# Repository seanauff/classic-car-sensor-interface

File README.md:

classic-car-sensor-interface
============================
Software to collect and display automotive sensor data on 16x2 LCD.
Written for use on Arduino MEGA2560, requires additional hardware to run.

Imgur album with pictures: https://imgur.com/gallery/zIYda

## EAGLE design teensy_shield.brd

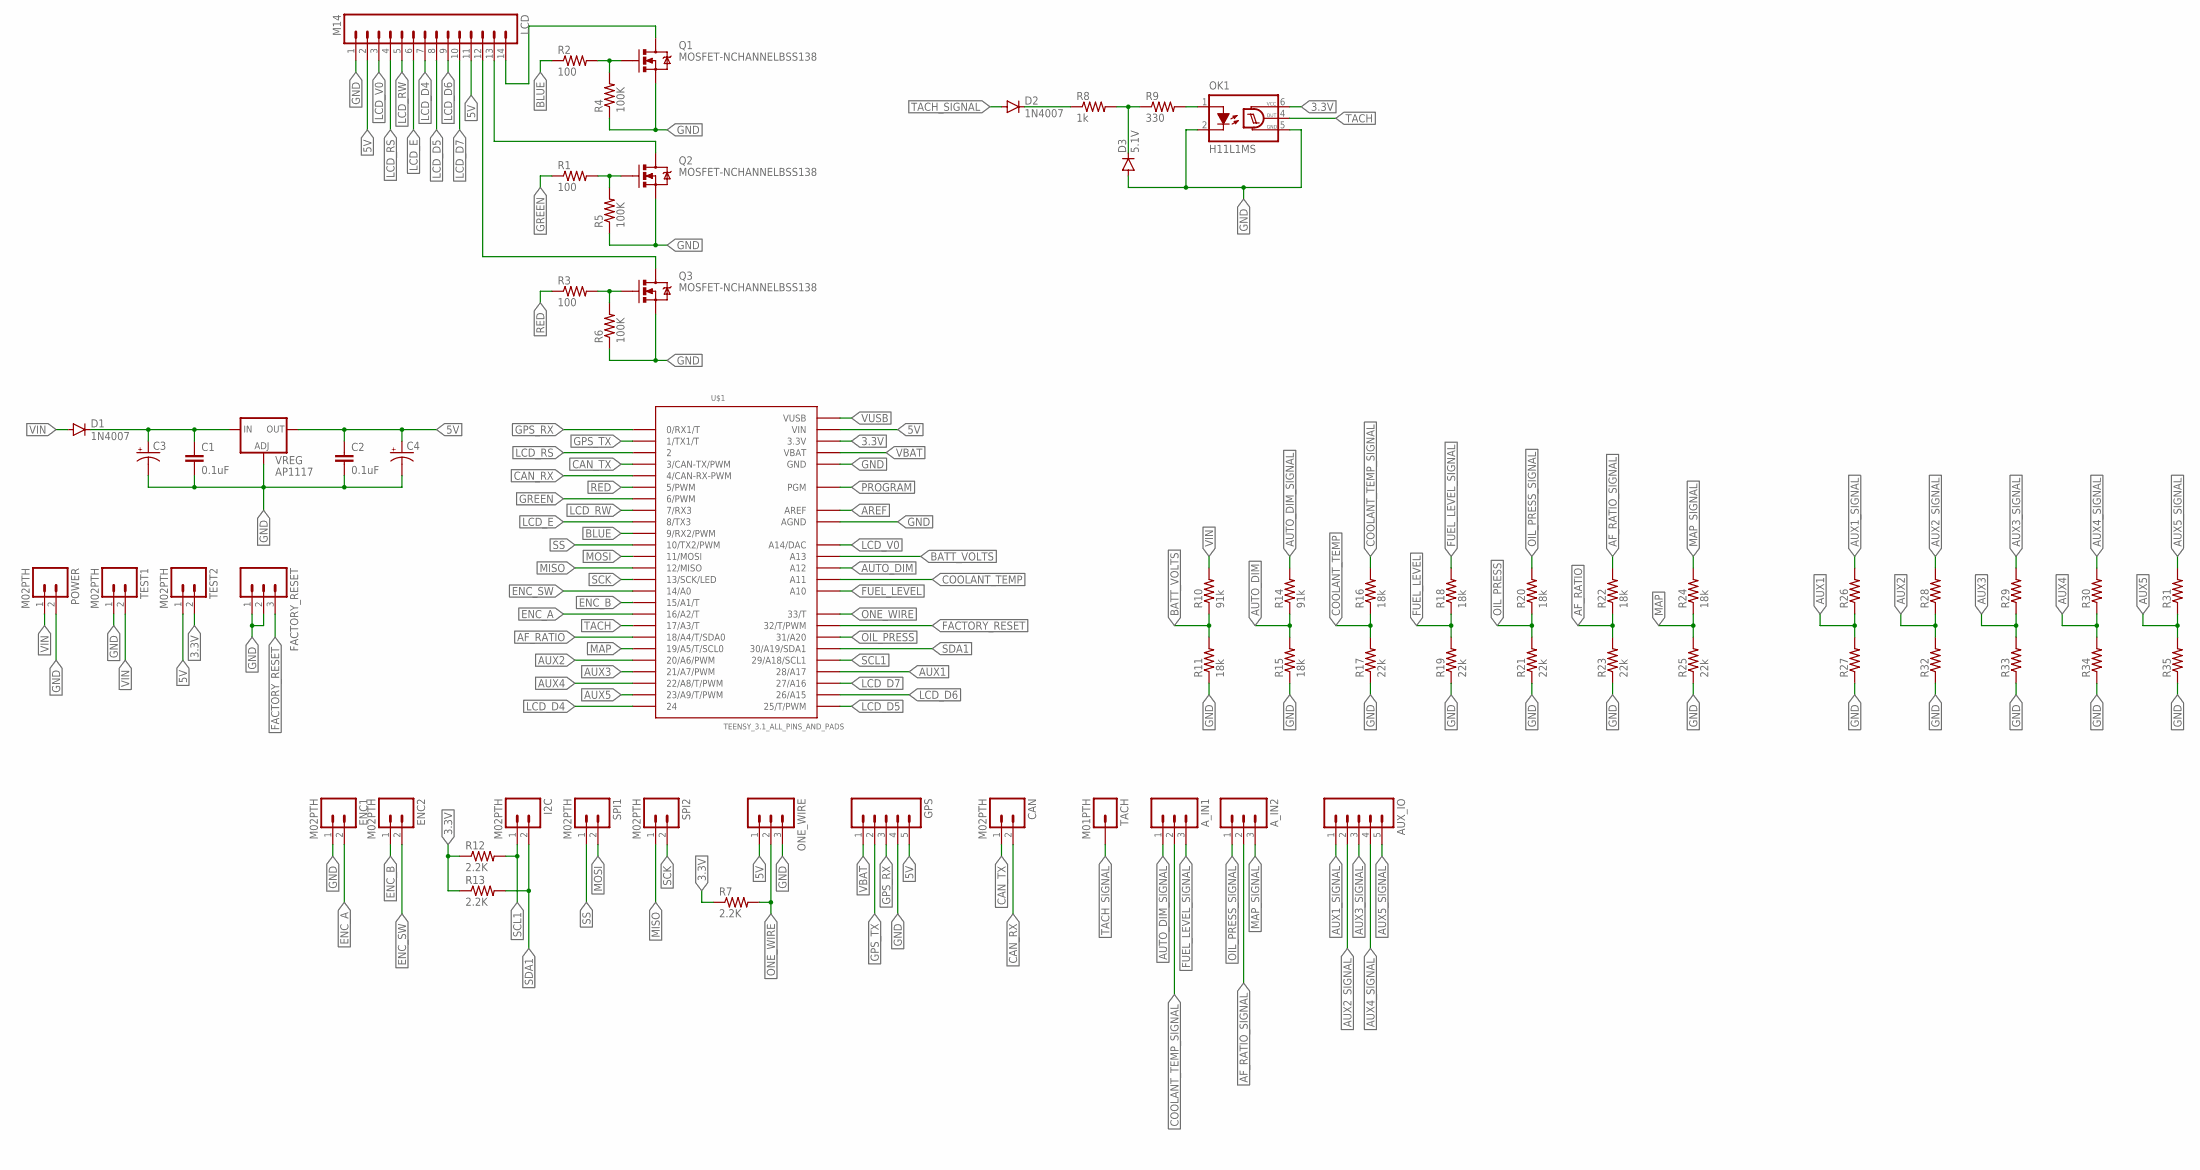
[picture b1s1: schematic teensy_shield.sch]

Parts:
AUX_IO: M05PTH; 1X05
A_IN1, A_IN2: M03PTH; 1X03
C1, C2: 0.1uF; 1206
C3, C4: CAP_POL6032; EIA6032
CAN: M02PTH; 1X02
D1, D2: 1N4007; SMA-DIODE_ALT
D3: 5.1V; SMA-DIODE_ALT
ENC1, ENC2: M02PTH; 1X02
FACTORY_RESET: M03PTH; 1X03
GPS: M05PTH; 1X05
I2C: M02PTH; 1X02
LCD: M14; 1X14
OK1: H11L1MS; DIL6-SMD
ONE_WIRE: M03PTH; 1X03
POWER: M02PTH; 1X02
Q1, Q2, Q3: MOSFET-NCHANNELBSS138; SOT23
R1, R2, R3: 100; 1206
R4, R5, R6: 100K; 1206
R7, R12, R13: 2.2K; 1206
R8: 1k; 1206
R9: 330; 1206
R10, R14: 91k; 1206
R11, R15, R16, R18, R20, R22, R24: 18k; 1206
R17, R19, R21, R23, R25: 22k; 1206
R26, R27, R28, R29, R30, R31, R32, R33, R34, R35: RESISTOR1206; 1206
SPI1, SPI2: M02PTH; 1X02
TACH: M01PTH; 1X01
TEST1, TEST2: M02PTH; 1X02
U$1: TEENSY_3.1_ALL_PINS_AND_PADS; TEENSY_3.1_ALLPINS
VREG: AP1117; SOT223

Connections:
3.3V: OK1.6 (VCC), R7.1, R12.1, R13.1, TEST2.2, U$1.3.3V, U$1.3.3V1 (3.3V), U$1.3.3V2 (3.3V)
5V: C2.1, C4.P$1 (+), GPS.5, LCD.2, LCD.11, ONE_WIRE.1, TEST2.1, U$1.VIN, VREG.2 (OUT)
AF_RATIO: R22.1, R23.2, U$1.18/A4 (18/A4/T/SDA0)
AF_RATIO_SIGNAL: A_IN2.2, R22.2
AREF: U$1.AREF
AUTO_DIM: R14.1, R15.2, U$1.A12
AUTO_DIM_SIGNAL: A_IN1.1, R14.2
AUX1: R26.1, R27.2, U$1.28 (28/A17)
AUX1_SIGNAL: AUX_IO.1, R26.2
AUX2: R28.1, R32.2, U$1.20/A6 (20/A6/PWM)
AUX2_SIGNAL: AUX_IO.2, R28.2
AUX3: R29.1, R33.2, U$1.21/A7 (21/A7/PWM)
AUX3_SIGNAL: AUX_IO.3, R29.2
AUX4: R30.1, R34.2, U$1.22/A8 (22/A8/T/PWM)
AUX4_SIGNAL: AUX_IO.4, R30.2
AUX5: R31.1, R35.2, U$1.23/A9 (23/A9/T/PWM)
AUX5_SIGNAL: AUX_IO.5, R31.2
BATT_VOLTS: R10.1, R11.2, U$1.A13
BLUE: R2.1, U$1.9 (9/RX2/PWM)
CAN_RX: CAN.2, U$1.4 (4/CAN-RX-PWM)
CAN_TX: CAN.1, U$1.3 (3/CAN-TX/PWM)
COOLANT_TEMP: R16.1, R17.2, U$1.A11
COOLANT_TEMP_SIGNAL: A_IN1.2, R16.2
ENC_A: ENC1.2, U$1.16/A2 (16/A2/T)
ENC_B: ENC2.1, U$1.15/A1 (15/A1/T)
ENC_SW: ENC2.2, U$1.14/A0
FACTORY_RESET: FACTORY_RESET.3, U$1.32 (32/T/PWM)
FUEL_LEVEL: R18.1, R19.2, U$1.A10
FUEL_LEVEL_SIGNAL: A_IN1.3, R18.2
GND: C1.2, C2.2, C3.P$2 (-), C4.P$2 (-), D3.A, ENC1.1, FACTORY_RESET.1, FACTORY_RESET.2, GPS.4, LCD.1, OK1.2 (C), OK1.5 (GND), ONE_WIRE.3, POWER.2, Q1.2 (S), Q2.2 (S), Q3.2 (S), R4.1, R5.1, R6.1, R11.1, R15.1, R17.1, R19.1, R21.1, R23.1, R25.1, R27.1, R32.1, R33.1, R34.1, R35.1, TEST1.1, U$1.AGND, U$1.GND, U$1.GND1 (GND), U$1.GND2 (GND), VREG.1 (ADJ)
GPS_RX: GPS.3, U$1.0 (0/RX1/T)
GPS_TX: GPS.2, U$1.1 (1/TX1/T)
GREEN: R1.1, U$1.6 (6/PWM)
LCD_D4: LCD.7, U$1.24
LCD_D5: LCD.8, U$1.25 (25/T/PWM)
LCD_D6: LCD.9, U$1.26 (26/A15)
LCD_D7: LCD.10, U$1.27 (27/A16)
LCD_E: LCD.6, U$1.8 (8/TX3)
LCD_RS: LCD.4, U$1.2
LCD_RW: LCD.5, U$1.7 (7/RX3)
LCD_V0: LCD.3, U$1.A14 (A14/DAC)
MAP: R24.1, R25.2, U$1.19/A5 (19/A5/T/SCL0)
MAP_SIGNAL: A_IN2.3, R24.2
MISO: SPI2.1, U$1.12 (12/MISO)
MOSI: SPI1.2, U$1.11 (11/MOSI)
unnamed: C1.1, C3.P$1 (+), D1.C, VREG.3 (IN)
unnamed: D2.C, R8.1
unnamed: D3.C, R8.2, R9.1
unnamed: OK1.1 (A), R9.2
unnamed: LCD.14, Q1.3 (D)
unnamed: LCD.13, Q2.3 (D)
unnamed: LCD.12, Q3.3 (D)
unnamed: Q1.1 (G), R2.2, R4.2
unnamed: Q2.1 (G), R1.2, R5.2
unnamed: Q3.1 (G), R3.2, R6.2
OIL_PRESS: R20.1, R21.2, U$1.31 (31/A20)
OIL_PRESS_SIGNAL: A_IN2.1, R20.2
ONE_WIRE: ONE_WIRE.2, R7.2, U$1.33 (33/T)
PROGRAM: U$1.PGM
RED: R3.1, U$1.5 (5/PWM)
SCK: SPI2.2, U$1.13 (13/SCK/LED)
SCL1: I2C.1, R12.2, U$1.29 (29/A18/SCL1)
SDA1: I2C.2, R13.2, U$1.30 (30/A19/SDA1)
SS: SPI1.1, U$1.10 (10/TX2/PWM)
TACH: OK1.4 (OUT), U$1.17/A3 (17/A3/T)
TACH_SIGNAL: D2.A, TACH.1
VBAT: GPS.1, U$1.VBAT
VIN: D1.A, POWER.1, R10.2, TEST1.2
VUSB: U$1.VUSB

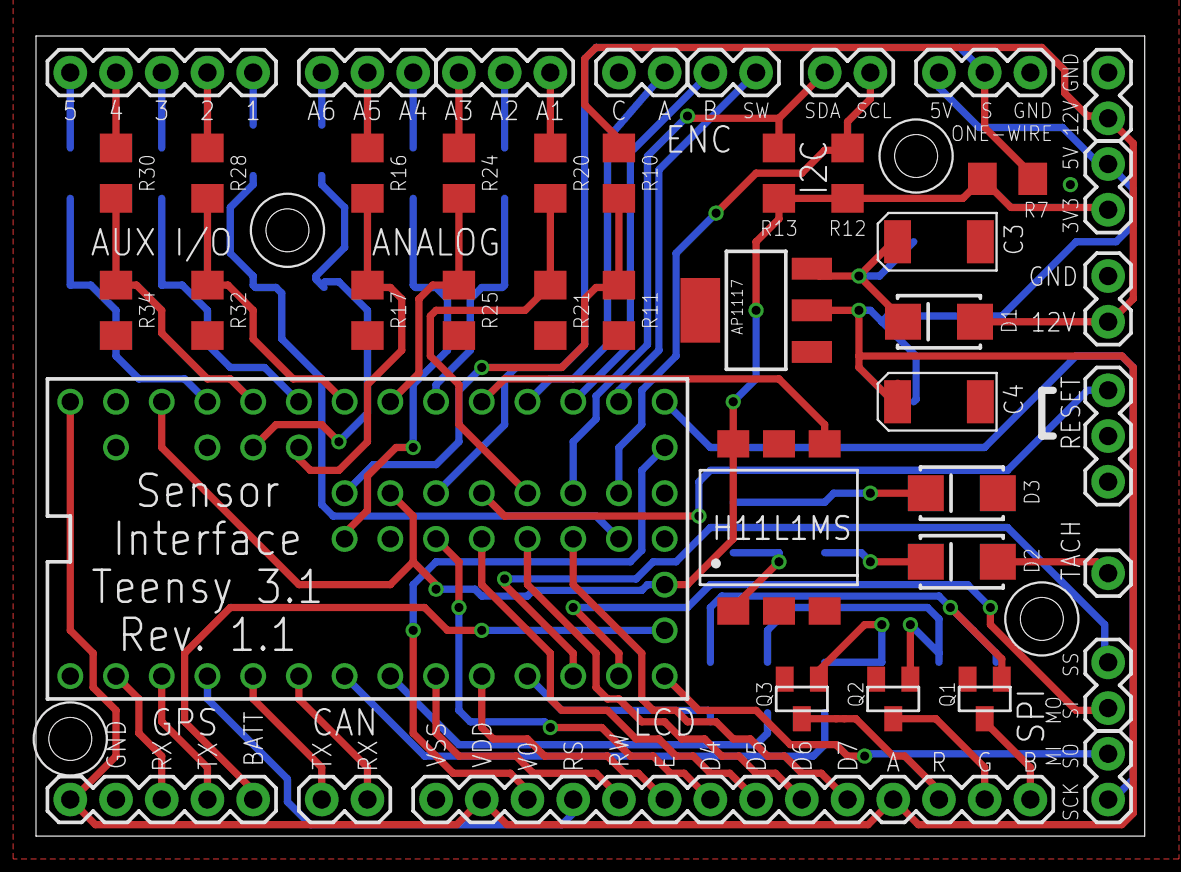
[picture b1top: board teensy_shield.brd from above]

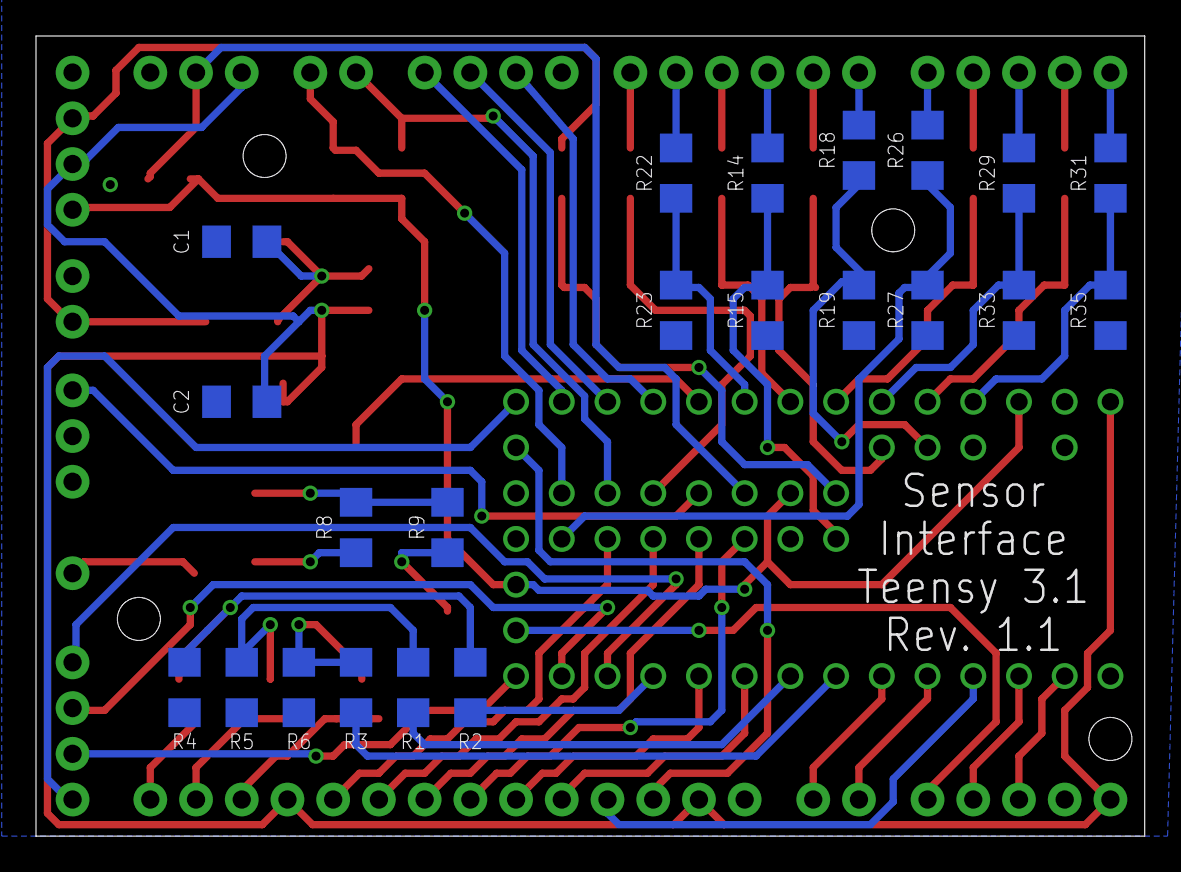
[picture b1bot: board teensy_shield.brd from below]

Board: 2 copper layers, 61.6 x 44.5 mm, 65 parts (22 on the bottom side), 66 nets.

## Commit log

2014-09-13 Update sensors.ino
    added RTC code, added ability to change number of engine cylinders, changed encoder switch to use built in pullup resistor, fixed major bug that would quickly destroy EEPROM integrity
2014-09-14 Update sensors.ino
    added ability to factory reset and change unit system in system settings menu
2014-09-17 Update sensors.ino
    contrast PWM freq increased to 32.5 kHz, more modifications to take advantage of internal pullups, analog inputs now uses an average of 10 samples, brightness no longer modified on boot
2014-09-18 Update sensors.ino
    UI tweaks, comment fixes, add A/F sensor code
2014-10-02 Update sensors.ino
    comments, organization improvements, improve analog read functionality, DS18B20 sensors now work properly
2014-10-02 Update sensors.ino
    formatting, comments
2014-10-08 Update sensors.ino
    Fix issue that would cause analog input functions to return incorrect values, updated S-H parameters to those for sender in use
2014-10-08 Update sensors.ino
    Fixed some display issues, fixed cases where floats were truncated to ints, now they are rounded
2014-10-09 Update sensors.ino
    Added ability to change sensor update interval, minor improvements and corrections
2014-10-13 Update sensors.ino
    factory reset improvements, auto dim brightness fix, new calibration curve for autometer 2242 oil pressure sensor
2014-10-13 Update sensors.ino
    now uses BigNumbers library for displaying big numbers, code readability improvements
2014-10-15 Update sensors.ino
    add intake pressure
2014-10-15 Update sensors.ino
    Better negative handling
2014-10-15 Update sensors.ino
    better negative number handling for small font display mode, fix oil pressure display, add beginnings of MAF display
2014-10-16 Update sensors.ino
    add displacement
2014-10-16 Update sensors.ino
    made a function to get the RPM, expanded MAFR calculation method
2014-10-22 Update sensors.ino
    now use LiquidCrystalFast
2014-11-08 Update and rename sensors.ino to sensor_interface.ino
    Performance and memory optimizations, less EEPROM writes for longer life, use new function available in BigNumbersFast library, more comments, MAFR calculation updates
2014-11-08 First release for Teensy 3.1
    Now works with Teensy 3.1.
    Bug fixed where encoder would sometimes not switch modes correctly. MAFR display added (large and small)
2014-11-08 Update sensor_interface_2560.ino
    bug fixed where modes would not switch correctly. MAFR updates
2014-11-17 Update sensor_interface_2560.ino
    added aRef variable, change modeUseCelcius to modeUseSI, change "English" to "SAE" for units, fix interrupt issue with tach, rearrange case statements in displayInfo to reflect order of modes
2014-11-18 Update sensor_interface_2560.ino
    Overhaul of displayInfo function to allow for easily adding extra features
2014-11-18 Update sensor_interface_2560.ino
    improve color changing, UI tweaks for settings
2014-11-18 Update sensor_interface_teensy_3_1.ino
    displayInfo() overhaul, color change improvements, UI tweaks
2014-12-02 Update sensor_interface_2560.ino
    add engine cycles
2014-12-02 Update sensor_interface_teensy_3_1.ino
    add engine cycles

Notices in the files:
parts and their libraries:
SparkFun-DiscreteSemi: Licensing: Creative Commons ShareAlike 4.0 International - https://creativecommons.org/licenses/by-sa/4.0
